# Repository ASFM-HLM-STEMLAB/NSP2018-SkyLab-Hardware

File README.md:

# NSP2018-SkyLab-Hardware
ASFM Near Space Program 2018 - SkyLab FlightComputer Hardware

## Welcome to NSP2018-SkyLab-Hardware repository
The flight computer consists of a *ESP32* Microcontroller in the Adafruit Feather form factor. 
[ESP32](https://www.adafruit.com/product/3405)

* Optionally we are waiting for Particle.io to release their new mesh line of MCUs. We love the development environment from Particle.io and their devices. For now we are awaiting for them to release the line, we should test compatibility when they do and hope for the best.<small>

This device contains an onboard GPS, LoRa Radio, SDCard and Internal Pressure and Temp Sensor. It is designed to interface with an optional external Iridium RockBlock Satelite Module:
[RockBlock Sat Modem](https://www.sparkfun.com/products/14498)

Also contains ports for external sensors, both in i2c and SPI. It also has a couple of mosfets for a buzzer and a beacon or optionally an electric match to prevent floaters.

See the attached BOM for details

The internal GPS is a U-Blox GPS picked because it allows the device to be effective above the 60,000ft gps limit.

Designed in Autodesk Eagle.
by: Francisco Lobo
at ASFM STEM LAB Monterrey
[HLM STEM-LAB Instagram](https://www.instagram.com/asfmstemlab/)

=======

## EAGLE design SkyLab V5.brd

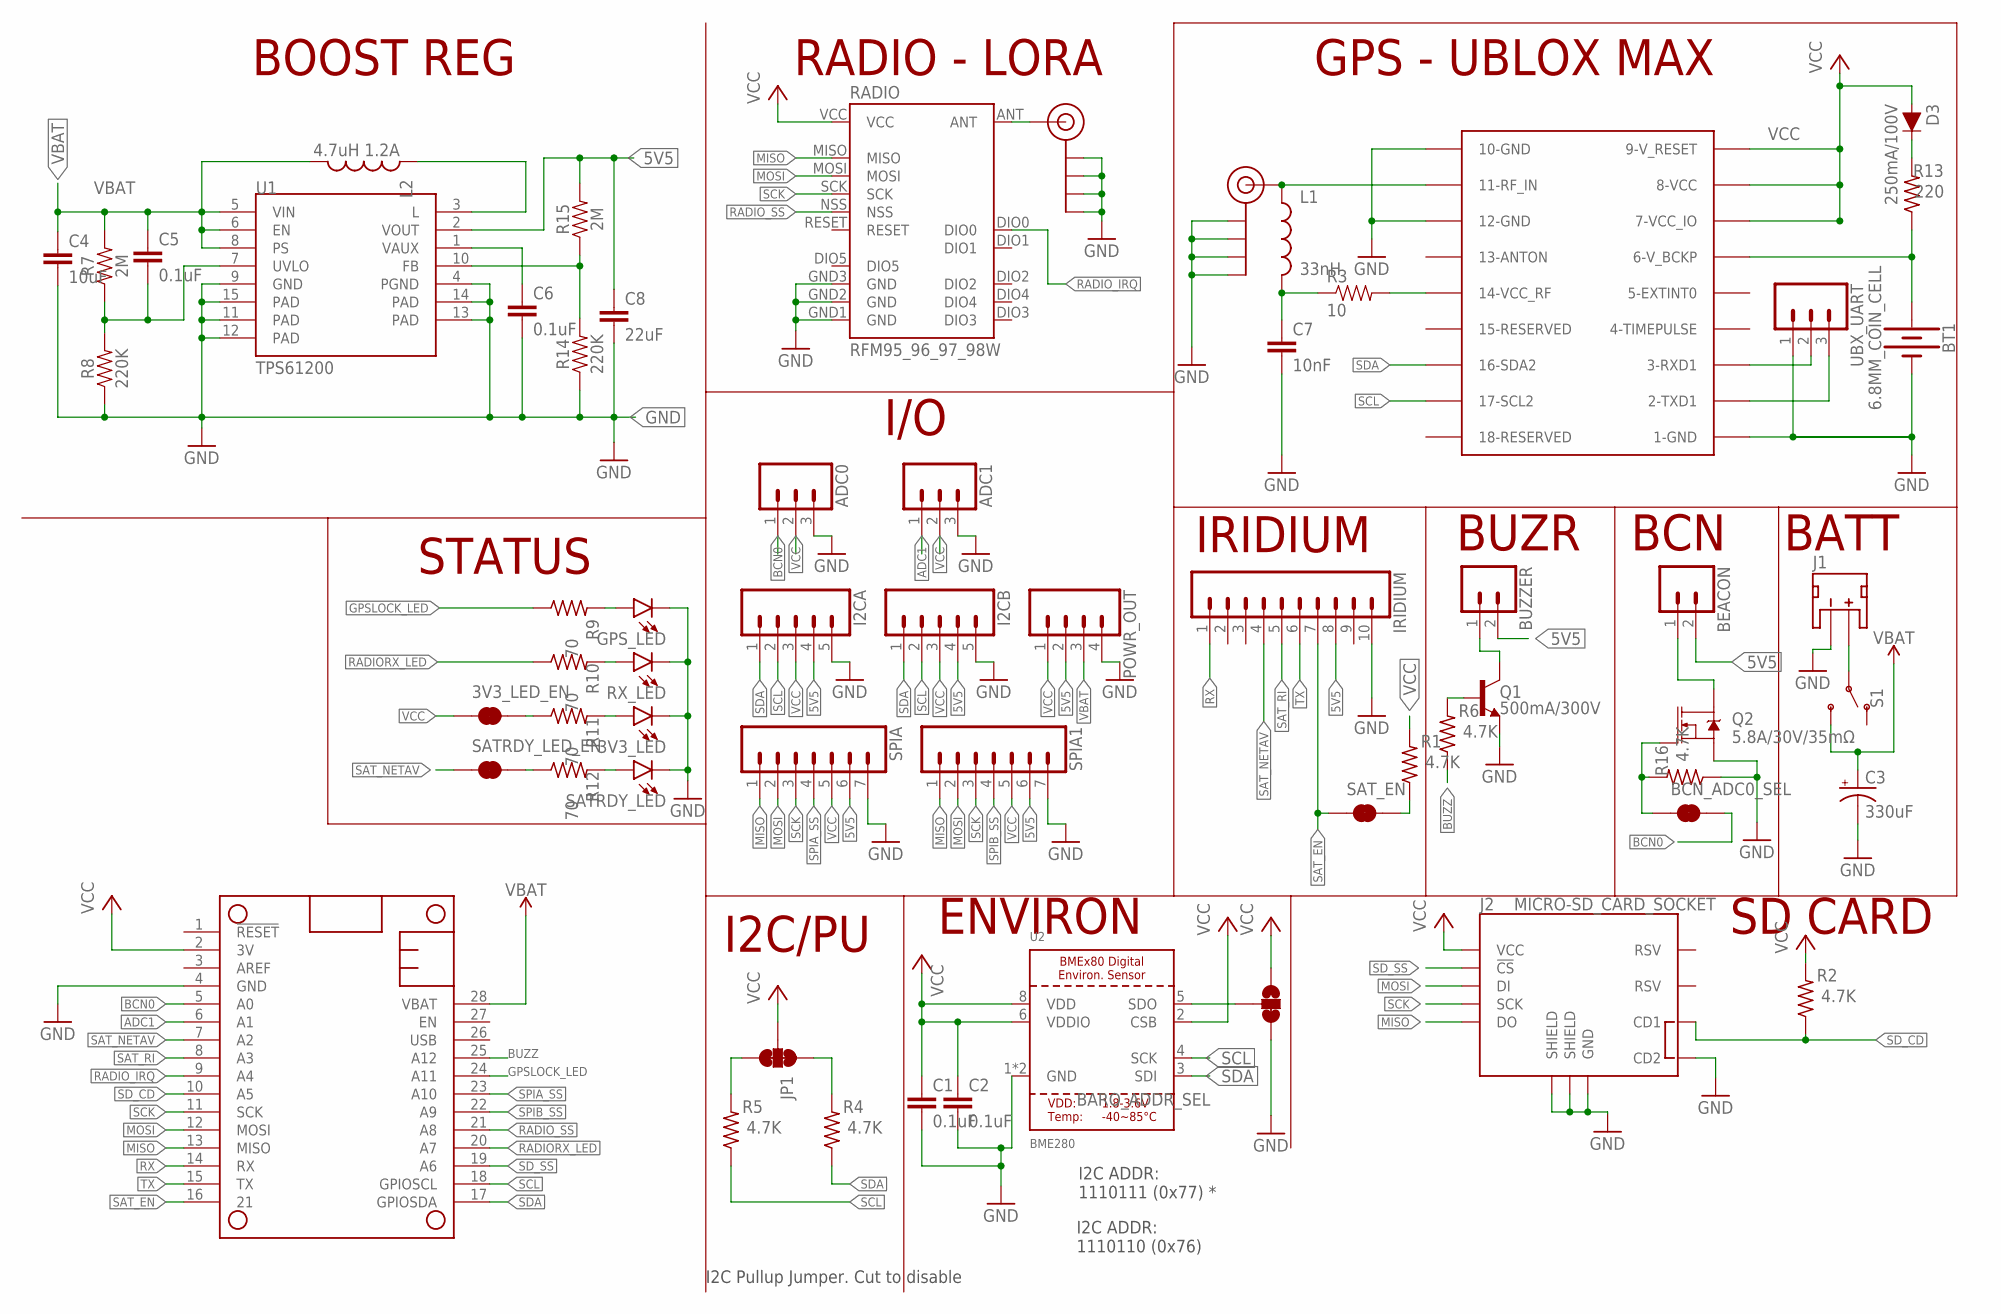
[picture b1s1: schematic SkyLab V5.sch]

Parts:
3V3_LED: LED1206; LED-1206
3V3_LED_EN: JUMPER-SMT_2_NC_TRACE_SILK; SMT-JUMPER_2_NC_TRACE_SILK
ADC0, ADC1: CONN_03; 1X03
BARO_ADDR_SEL: JUMPER-SMT_3_1-NC_TRACE_SILK; SMT-JUMPER_3_1-NC_TRACE_SILK
BCN_ADC0_SEL: JUMPER-SMT_2_NC_TRACE_SILK; SMT-JUMPER_2_NC_TRACE_SILK
BEACON: CONN_02; 1X02
BT1: 6.8MM_COIN_CELL; BATTCON-6.8MM
BUZZER: CONN_02; 1X02
C1, C2, C5, C6: 0.1uF; 0603
C3: 330uF; EIA6032
C4: 10uF; 1206
C7: 10nF; 0603
C8: 22uF; 0805
D3: 250mA/100V; SOD-323
GPS_ANT: SMA_EDGE; SMA-EDGE
GPS_LED: LED1206; LED-1206
I2CA, I2CB: CONN_05; 1X05
IRIDIUM: CONN_10"; 1X10
J1: JST_2MM_MALE; JST-2-SMD
J2: MICRO-SD_CARD_SOCKET; MICRO-SD-SOCKET
JP1: JUMPER-SMT_3_2-NC_TRACE_SILK; SMT-JUMPER_3_2-NC_TRACE_SILK
L1: 33nH; 0603
L2: 4.7uH 1.2A; 0603
MS1: FEATHERWING_NODIM; FEATHERWING_DIM
POWR_OUT: CONN_04; 1X04
Q1: 500mA/300V; SOT23-3
Q2: 5.8A/30V/35mΩ; SOT23-3
R1, R2, R4, R5, R6, R16: 4.7K; M0805
R3: 10; 0603-RES
R7, R15: 2M; 0805
R8, R14: 220K; 0805
R9, R10, R11, R12: 70; M0805
R13: 220; M0805
RADIO: RFM95_96_97_98W
RDIO_ANT: SMA_EDGE; SMA-EDGE
RX_LED: LED1206; LED-1206
S1: SWITCH-SPDT-SMD-RIGHT-ANGLE; SWITCH_SPST_SMD_A
SATRDY_LED: LED1206; LED-1206
SATRDY_LED_EN: JUMPER-SMT_2_NC_TRACE_SILK; SMT-JUMPER_2_NC_TRACE_SILK
SAT_EN: JUMPER-SMT_2_NC_TRACE_SILK; SMT-JUMPER_2_NC_TRACE_SILK
SPIA, SPIA1: CONN_07; 1X07
U1: TPS61200; QFN-10_PAD
U2: BME280
UBLOX: UBLOX_MAX
UBX_UART: CONN_03; 1X03

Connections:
5V5: BEACON.2, BUZZER.2, C8.1, I2CA.4, I2CB.4, IRIDIUM.8, POWR_OUT.2, R15.2, SPIA.6, SPIA1.6, U1.2 (VOUT)
ADC1: ADC1.1, MS1.6 (A1)
BCN0: ADC0.1, BCN_ADC0_SEL.2, MS1.5 (A0)
BUZZ: MS1.25 (A12), R6.1
EDITINF: BCN_ADC0_SEL.1, Q2.1 (G), R16.2
GND: 3V3_LED.C, ADC0.3, ADC1.3, BARO_ADDR_SEL.3, BT1.-, C1.2, C2.2, C3.P$2 (-), C4.2, C6.2, C7.2, C8.2, GPS_ANT.GND@0 (GND), GPS_ANT.GND@1 (GND), GPS_ANT.GND@2 (GND), GPS_ANT.GND@3 (GND), GPS_LED.C, I2CA.5, I2CB.5, IRIDIUM.10, J1.1 (-), J2.CD2, J2.GND, J2.GND1 (SHIELD), J2.GND3 (SHIELD), MS1.4 (GND), POWR_OUT.4, Q1.2 (E), Q2.2 (S), R8.1, R14.1, R16.1, RADIO.GND1 (GND), RADIO.GND2 (GND), RADIO.GND3 (GND), RDIO_ANT.GND@0 (GND), RDIO_ANT.GND@1 (GND), RDIO_ANT.GND@2 (GND), RDIO_ANT.GND@3 (GND), RX_LED.C, SATRDY_LED.C, SPIA.7, SPIA1.7, U1.4 (PGND), U1.9 (GND), U1.11 (PAD), U1.12 (PAD), U1.13 (PAD), U1.14 (PAD), U1.15 (PAD), U2.1 (GND), U2.7 (GND), UBLOX.1-GND, UBLOX.10-GND, UBLOX.12-GND, UBX_UART.1
GPSLOCK_LED: MS1.24 (A11), R9.1
MISO: J2.DO, MS1.13 (MISO), RADIO.MISO, SPIA.1, SPIA1.1
MOSI: J2.DI, MS1.12 (MOSI), RADIO.MOSI, SPIA.2, SPIA1.2
unnamed: R1.1, SAT_EN.2
unnamed: GPS_ANT.SIG (SIGNAL), L1.1, UBLOX.11-RFIN (11-RF_IN)
unnamed: C7.1, L1.2, R3.1
unnamed: R3.2, UBLOX.14-VCC_RF
unnamed: RADIO.ANT, RDIO_ANT.SIG (SIGNAL)
unnamed: JP1.3, R5.2
unnamed: JP1.1, R4.2
unnamed: Q1.1 (B), R6.2
unnamed: BUZZER.1, Q1.3 (C)
unnamed: GPS_LED.A, R9.2
unnamed: BT1.+, R13.1, UBLOX.6-V_BCKP
unnamed: R12.1, SATRDY_LED_EN.2
unnamed: R10.2, RX_LED.A
unnamed: 3V3_LED.A, R11.2
unnamed: 3V3_LED_EN.2, R11.1
unnamed: D3.C, R13.2
unnamed: BARO_ADDR_SEL.2, U2.5 (SDO)
unnamed: R12.2, SATRDY_LED.A
unnamed: C5.2, R7.1, R8.2, U1.7 (UVLO)
unnamed: UBLOX.3-RXD1, UBX_UART.2
unnamed: UBLOX.2-TXD1, UBX_UART.3
unnamed: R14.2, R15.1, U1.10 (FB)
unnamed: L2.1, U1.3 (L)
unnamed: C6.1, U1.1 (VAUX)
unnamed: BEACON.1, Q2.3 (D)
RADIORX_LED: MS1.20 (A7), R10.1
RADIO_IRQ: MS1.9 (A4), RADIO.DIO0
RADIO_SS: MS1.21 (A8), RADIO.NSS
RX: IRIDIUM.1, MS1.14 (RX)
SAT_EN: IRIDIUM.7, MS1.16 (21), SAT_EN.1
SAT_NETAV: IRIDIUM.4, MS1.7 (A2), SATRDY_LED_EN.1
SAT_RI: IRIDIUM.5, MS1.8 (A3)
SCK: J2.SCLK (SCK), MS1.11 (SCK), RADIO.SCK, SPIA.3, SPIA1.3
SCL: I2CA.2, I2CB.2, MS1.18 (GPIOSCL), R5.1, U2.4 (SCK), UBLOX.17-SCL2
SDA: I2CA.1, I2CB.1, MS1.17 (GPIOSDA), R4.1, U2.3 (SDI), UBLOX.16-SDA2
SD_CD: J2.CD1, MS1.10 (A5), R2.1
SD_SS: J2.CS (!CS), MS1.19 (A6)
SPIA_SS: MS1.23 (A10), SPIA.4
SPIB_SS: MS1.22 (A9), SPIA1.4
TX: IRIDIUM.6, MS1.15 (TX)
VBAT: C3.P$1 (+), C4.1, C5.1, L2.2, MS1.28 (VBAT), POWR_OUT.3, R7.2, S1.3 (S), U1.5 (VIN), U1.6 (EN), U1.8 (PS)
VBAT_SUPPLY: J1.2 (+), S1.2
VCC: 3V3_LED_EN.1, ADC0.2, ADC1.2, BARO_ADDR_SEL.1, C1.1, C2.1, D3.A, I2CA.3, I2CB.3, J2.VCC, JP1.2, MS1.2 (3V), POWR_OUT.1, R1.2, R2.2, RADIO.VCC, SPIA.5, SPIA1.5, U2.2 (CSB), U2.6 (VDDIO), U2.8 (VDD), UBLOX.7-VCC_IO, UBLOX.8-VCC, UBLOX.9-V_RESET

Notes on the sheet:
GPS - UBLOX MAX
BOOST REG
RADIO - LORA
IRIDIUM
I/O
BUZR
BATT
I2C/PU
I2C Pullup Jumper. Cut to disable
I2C ADDR: 1110110 (0x76)
I2C ADDR: 1110111 (0x77) *
ENVIRON
SD CARD
STATUS
BCN

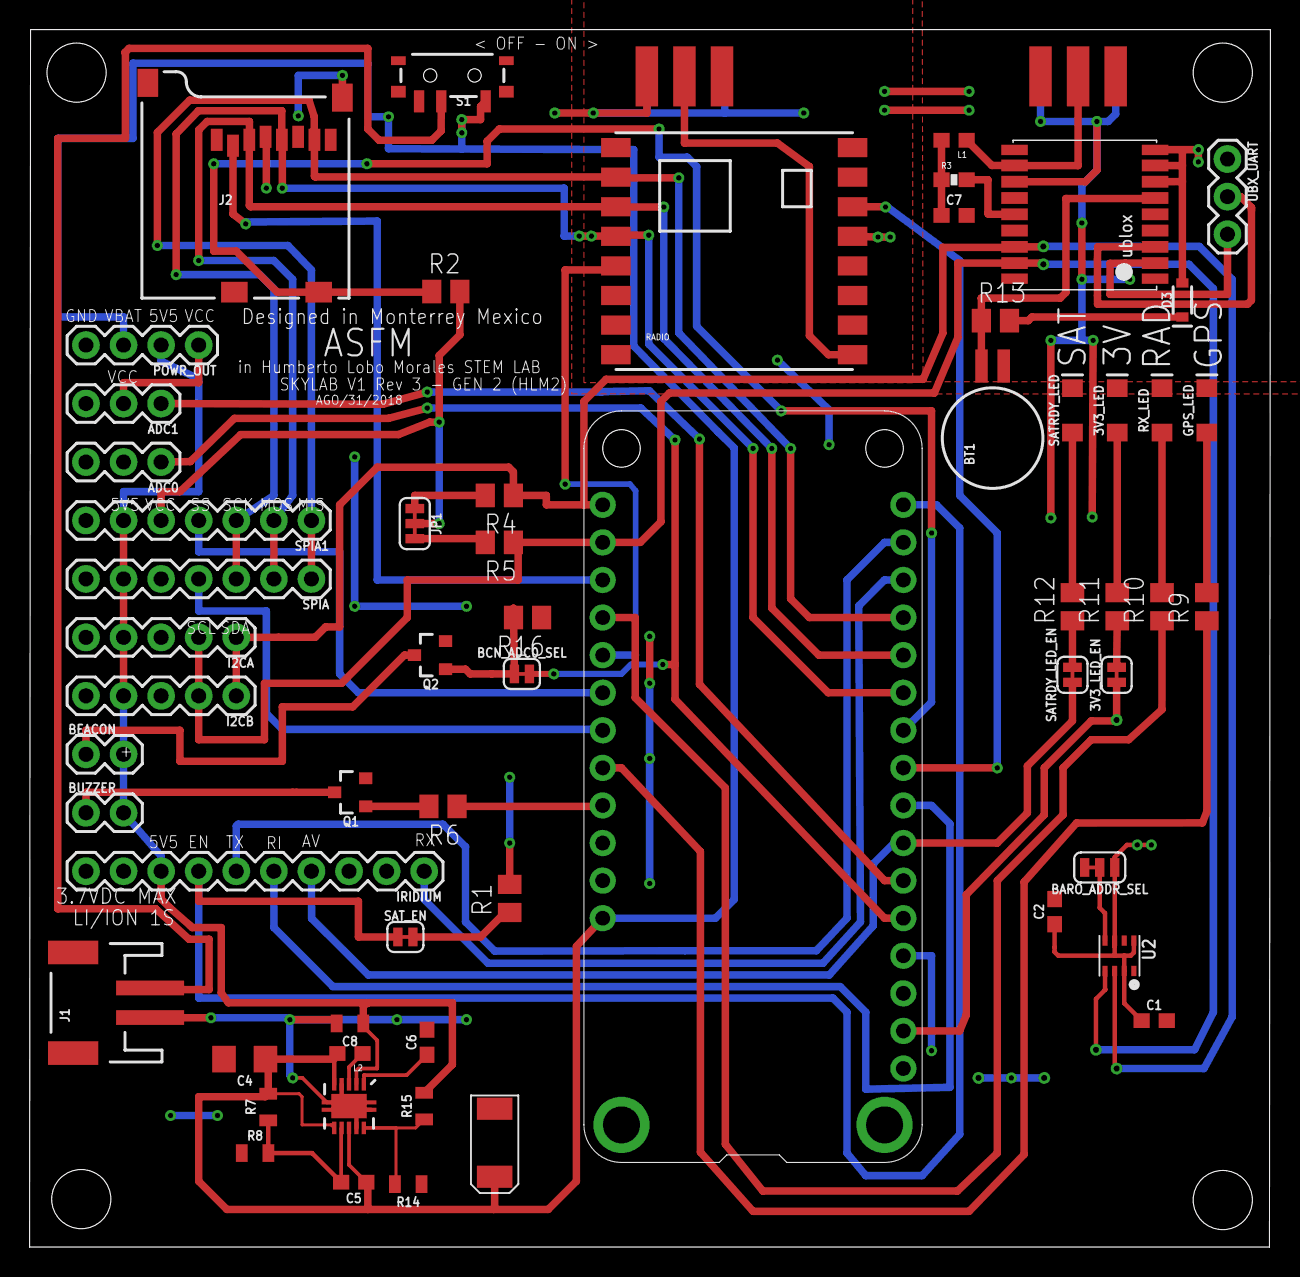
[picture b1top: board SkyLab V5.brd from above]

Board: 2 copper layers, 83.9 x 82.3 mm, 61 parts (0 on the bottom side), 52 nets.

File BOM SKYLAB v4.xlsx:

Part | Value | VALUE | Package | Part. No. | Description | DigiKey URL | PROD_ID | SF_ID | SF_SKU
R3 | 10 |  | 603 | MCT06030C1009FP500 | Resistor | https://www.digikey.com/product-detail/en/vishay-beyschlag/M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
R13 | 220 |  | M0805 | ERJ-PB6D2200V | RESISTOR, American symbol | https://www.digikey.com/product-detail/en/panasonic-electron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
R9 | 330 |  | M0805 | P330CDKR-ND | RESISTOR, American symbol | https://www.digikey.com/product-detail/en/panasonic-electron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
R10 | 330 |  | M0805 | P330CDKR-ND | RESISTOR, American symbol | https://www.digikey.com/product-detail/en/panasonic-electron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
R11 | 330 |  | M0805 | P330CDKR-ND | RESISTOR, American symbol | https://www.digikey.com/product-detail/en/panasonic-electron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
R12 | 330 |  | M0805 | P330CDKR-ND | RESISTOR, American symbol | https://www.digikey.com/product-detail/en/panasonic-electron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
C1 | 0.1uF | 0.1uF | 603 | CC0603ZRY5V9BB104 | 0.1¬µF ceramic capacitors | https://www.digikey.com/product-detail/en/yageo/CC0603ZRY5V9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 | CAP-00810
C2 | 0.1uF | 0.1uF | 603 | CC0603ZRY5V9BB104 | 0.1¬µF ceramic capacitors | https://www.digikey.com/product-detail/en/yageo/CC0603ZRY5V9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 | CAP-00810
C5 | 0.1uF | 0.1uF | 603 | CC0603ZRY5V9BB104 | 0.1¬µF ceramic capacitors | https://www.digikey.com/product-detail/en/yageo/CC0603ZRY5V9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 | CAP-00810
C6 | 0.1uF | 0.1uF | 603 | CC0603ZRY5V9BB104 | 0.1¬µF ceramic capacitors | https://www.digikey.com/product-detail/en/yageo/CC0603ZRY5V9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 | CAP-00810
C4 | 10uF | 10uF | 1206 | CL31A106KPHNNNE | 10.0¬µF ceramic capacitors | https://www.digikey.com/product-detail/en/samsung-electro-me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 | CAP-10057
R8 | 220K | 0.22 | 805 | KTR10EZPF2203 | 0.22Œ© resistor | https://www.digikey.com/product-detail/en/rohm-semiconductor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 | RES-09883
R14 | 220K | 0.22 | 805 | KTR10EZPF2203 | 0.22Œ© resistor | https://www.digikey.com/product-detail/en/rohm-semiconductor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 | RES-09883
C8 | 22uF | 22uF | 805 | CL21A226KPCLRNC | 22¬µF ceramic capacitors | https://www.digikey.com/product-detail/en/samsung-electro-me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 | CAP-08402
D3 | 250mA/100V | 250mA/100V | SOD-323 | 1N4148WSF | Diode 250mA/100V | https://www.digikey.com/product-detail/en/diodes-incorporate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 | DIO-09646
R7 | 2M | 0.22 | 805 | RC0805FR-072ML | 0.22Œ© resistor | https://www.digikey.com/product-detail/en/yageo/RC0805FR-072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 | RES-09883
R15 | 2M | 0.22 | 805 | RC0805FR-072ML | 0.22Œ© resistor | https://www.digikey.com/product-detail/en/yageo/RC0805FR-072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 | RES-09883
C3 | 330uF |  | EIA6032 | TPSC337K006R0080 | Capacitor Polarized | https://www.digikey.com/product-detail/en/TPSC337K006R0080/4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
L1 | 33nH |  | 603 | LQW18AN33NJ00D | Inductors | https://www.digikey.com/product-detail/en/murata-electronics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
R1 | 4.7K |  | M0805 | ESR10EZPJ472 | RESISTOR, American symbol | https://www.digikey.com/product-detail/en/rohm-semiconductor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
R2 | 4.7K |  | M0805 | ESR10EZPJ472 | RESISTOR, American symbol | https://www.digikey.com/product-detail/en/rohm-semiconductor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
R4 | 4.7K |  | M0805 | ESR10EZPJ472 | RESISTOR, American symbol | https://www.digikey.com/product-detail/en/rohm-semiconductor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
R5 | 4.7K |  | M0805 | ESR10EZPJ472 | RESISTOR, American symbol | https://www.digikey.com/product-detail/en/rohm-semiconductor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
R6 | 4.7K |  | M0805 | ESR10EZPJ472 | RESISTOR, American symbol | https://www.digikey.com/product-detail/en/rohm-semiconductor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
R16 | 4.7K |  | M0805 | ESR10EZPJ472 | RESISTOR, American symbol | https://www.digikey.com/product-detail/en/rohm-semiconductor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
L2 | 4.7uH 1.2A |  | 603 | MBKK1608T4R7M | Inductors | https://www.digikey.com/product-detail/en/taiyo-yuden/MBKK16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
Q2 | 5.8A/30V/35mŒ© | 5.8A/30V/35mŒ© | SOT23-3 | SSM3K333R,LF | N-channel MOSFETs | https://www.digikey.com/product-detail/en/toshiba-semiconduc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 | TRANS-12988
Q1 | 500mA/300V | 500mA/300V | SOT23-3 | ZXTN19020DFFTA | NPN transistor | https://www.digikey.com/product-detail/en/diodes-incorporate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 | TRANS-09116
BT1 | 6.8MM_CELL | 6.8MM_COIN_CELL | BATT-6.8MM | MS621FE-FL11E | Battery - Single Cell | https://www.digikey.com/product-detail/en/seiko-instruments/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 | BATT-13734
U2 | BME680 |  | LGA3.0X3.0 | BME680 | BME 680 - Sensor | https://www.digikey.com/product-detail/en/bosch-sensortec/BM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
LED | Green |  | LED-1206 | LTST-C150GKT‎ | LED (Generic) | https://www.digikey.com/product-detail/en/lite-on-inc/LTST-C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
LED | Green |  | LED-1206 | LTST-C150GKT‎ | LED (Generic) | https://www.digikey.com/product-detail/en/lite-on-inc/LTST-C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
LED | Green |  | LED-1206 | LTST-C150GKT‎ | LED (Generic) | https://www.digikey.com/product-detail/en/lite-on-inc/LTST-C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
LED | Green |  | LED-1206 | LTST-C150GKT‎ | LED (Generic) | https://www.digikey.com/product-detail/en/lite-on-inc/LTST-C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
J2 | SD_SOCKET |  | SD_SOCKET | 5031821852 | microSD Socket for Transflash | https://www.digikey.com/product-detail/en/molex-llc/50318218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 | CONN-07820 | PRT-00127
RADIO | RFM95W |  | RFM95W | RFM95W-915S2-ND | LoRA Radio | https://www.digikey.com/product-detail/en/rf-solutions/RFM95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
GPS_ANT | SMA_EDGE |  | SMA-EDGE | 132255RP | SMA Antenna Connector | https://www.digikey.com/product-detail/en/amphenol-rf-divisi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
RDIO_ANT | SMA_EDGE |  | SMA-EDGE | CON-SMA-EDGE-S | SMA Antenna Connector | https://www.digikey.com/product-detail/en/rf-solutions/CON-S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
U1 | TPS61200 |  | QFN-10_PAD | TPS61200DRCT | DC to DC Booster | https://www.digikey.com/product-detail/en/texas-instruments/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 | IC-10035
UBLOX | UBLOX_MAX |  | UBLOX_MAX | MAX-M8W-0 | UBLOX MAX | https://www.digikey.com/product-detail/en/u-blox-america-inc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
J1 |  |  | JST-2-SMD | S2B-PH-SM4-TB(LF)(SN) | JST 2MM MALE RA CONNECTOR | https://www.digikey.com/product-detail/en/jst-sales-america-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 | CONN-11443 | PRT-08612
S1 |  |  | SWTCH | PCM12SMTR | Single Pole, Double Throw (SPDT) Switch | https://www.digikey.com/product-detail/en/c-k/PCM12SMTR/401-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 | SWCH-10651 |  | COM-10860

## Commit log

2018-09-17 Updated BOM for V5

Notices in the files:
parts and their libraries:
SparkFun-LED: Licensing: Creative Commons ShareAlike 4.0 International - https://creativecommons.org/licenses/by-sa/4.0
